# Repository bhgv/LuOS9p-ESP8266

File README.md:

luOS9p
------

It is an OS for ESP8266 IoT microcontrollers based on Lua-RTOS-ESP8266. But it was significally checked, changed and expanded.

https://youtu.be/ojTmyH3cTSQ

[schemaic+pcb](pcb/eagle) (Eagle CAD)

Features
========
* Lua 5.3.4,
* Multithreading using Free-RTOS,
* UART (ttl rs232, com port),
* I2C,
* SPI,
* 16 PWMs (hardware),
* 16 PIOs,
* 5 ADC (3 up to 3v + 1 up to 1v + 1 used internally),
* 1 DAC (up to 3v),
* OLED screen,
* Keyboard with 8 buttons (cursor + 3 special + 1 external),
* GUI (menu based. using OLED and keyboard),
* Shell by remote (rs232) terminal,
* internal Editor of files (remote terminal),
* big set of easy to use shell commands (filesystem, ports, devices, network, server, other)
* net Ap and Sta modes,
* one command WiFi Sta search,
* PID regulator module,

* Webserver (with compressing):
  1. static HTML,
  1. CGI,
  1. WebSock (up to 5 connections),
  1. direct access to devices/ports using WebSock,

* 9p2000/Styx (Plan9/Inferno os) distributed network virtual file system + server:
  1. list of devices (ex: `ls /n/dev`),
  1. list of device's functions (ex: `cat /n/dev/pwm`),
  1. call a device's function (ex: `echo ch_val -i 5 -n 0.4 > /n/dev/pwm`),
  1. read the result of the function's call (ex: `<> /n/dev/pwm {echo ch_val -i 5 >[1=0]; read}`),
  1. read a file/folder list from the fisical filesystem of the device (ex: `ls /n/fs/html/js`),
  1. read/write/create files on the device's fisical filesystem (ex: `cat /n/fs/html/js/common.js` or `echo a Text > /n/fs/afile.txt`),
  1. create new folders on the device's fisical filesystem (ex: `mkdir /n/fs/new_folder`),
  1. remove files or folders from the fisical device's filesystem (ex: `rm /n/fs/html/a_file_or_folder`),
  1. RPC channel (synthetic file `/rpc`). it allows to send Lua chunk to the device, run it there and return the result. (ex: `<> /n/rpc {echo 'pwm[5] = 0.2; return "adc_1=", adc[1];' >[1=0]; read}`),
  1. user's CGI-like synthetic files. (ex: on the remote device: `styx.addfile("a_file", function(a) return a + 8; end);`, from the inferno-shell: `<> /n/a_file {echo -n 10.9 >[1=0]; read}`).

* PC-Studio for easyer upload/download/edit files into/from/on the luOS9p embedded filesystem. also PC-Studio contains remote terminal for luOS9p and other features (in the future). It is written on the Lua and may be edited/expanded easily. It also contains a plugin system for extensions, but it isn't activated for now.

How to build
============
```
./bld.sh    # build
./flash.sh  # flash
```

How to build PC-Studio
======================
```
cd pc-studio
./bld.sh
```

How to run PC-Studio
====================
```
cd pc-studio/bld
./prg
```

How to run Styx server
======================
In the device's console or from the lua script:
```
thread.start( styx.loop )
```
Or just select `Styx server` on the device's gui if you are using LuOS9p-PCB (or other with ported GUI driver)

In the inferno shell/script/limbo etc:
```
mount -A tcp!<IP address of your device>!6701 /n
```
Now your IoT device's styx virtual fs is mounted to `/n` folder, including branches for drivers `/dev` and for access to the fisical filesystem of the your IoT device `/fs`. Use it as a regular filesystem.

A special board for the luOS9p
==============================
For this OS was designed a [special PCB](pcb/eagle/) that included all the necessary hardware/drivers and supports all the features of the OS.

But the OS may be used with the most esp8266-based boards (maybe with changes in the drivers part of the OS according to the target hardware)

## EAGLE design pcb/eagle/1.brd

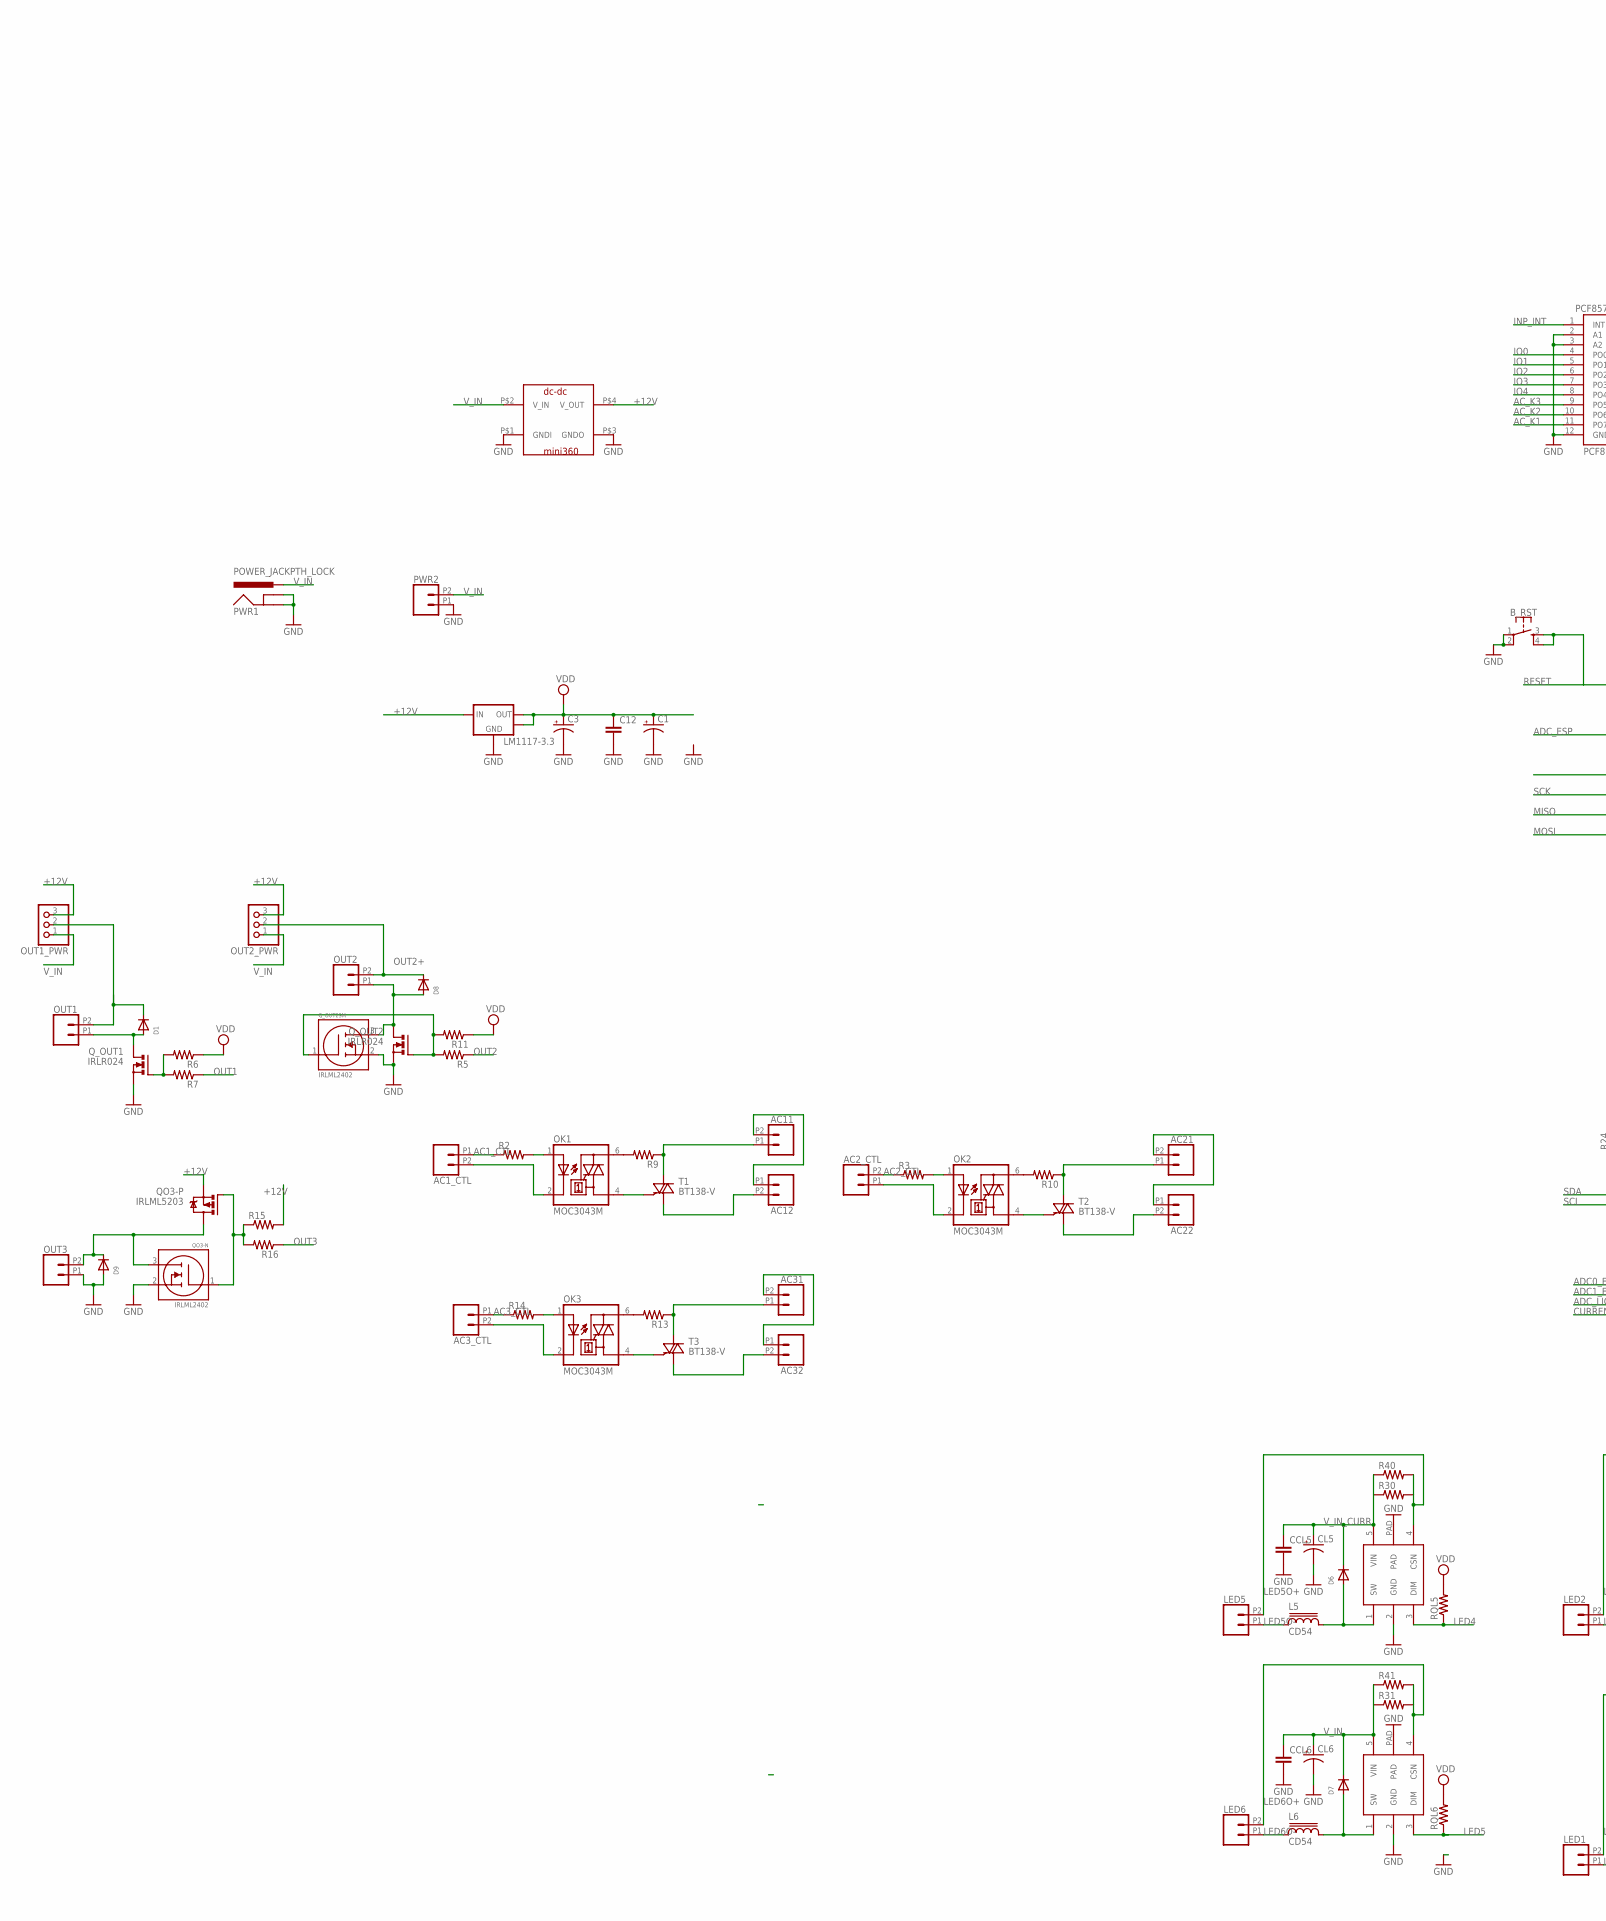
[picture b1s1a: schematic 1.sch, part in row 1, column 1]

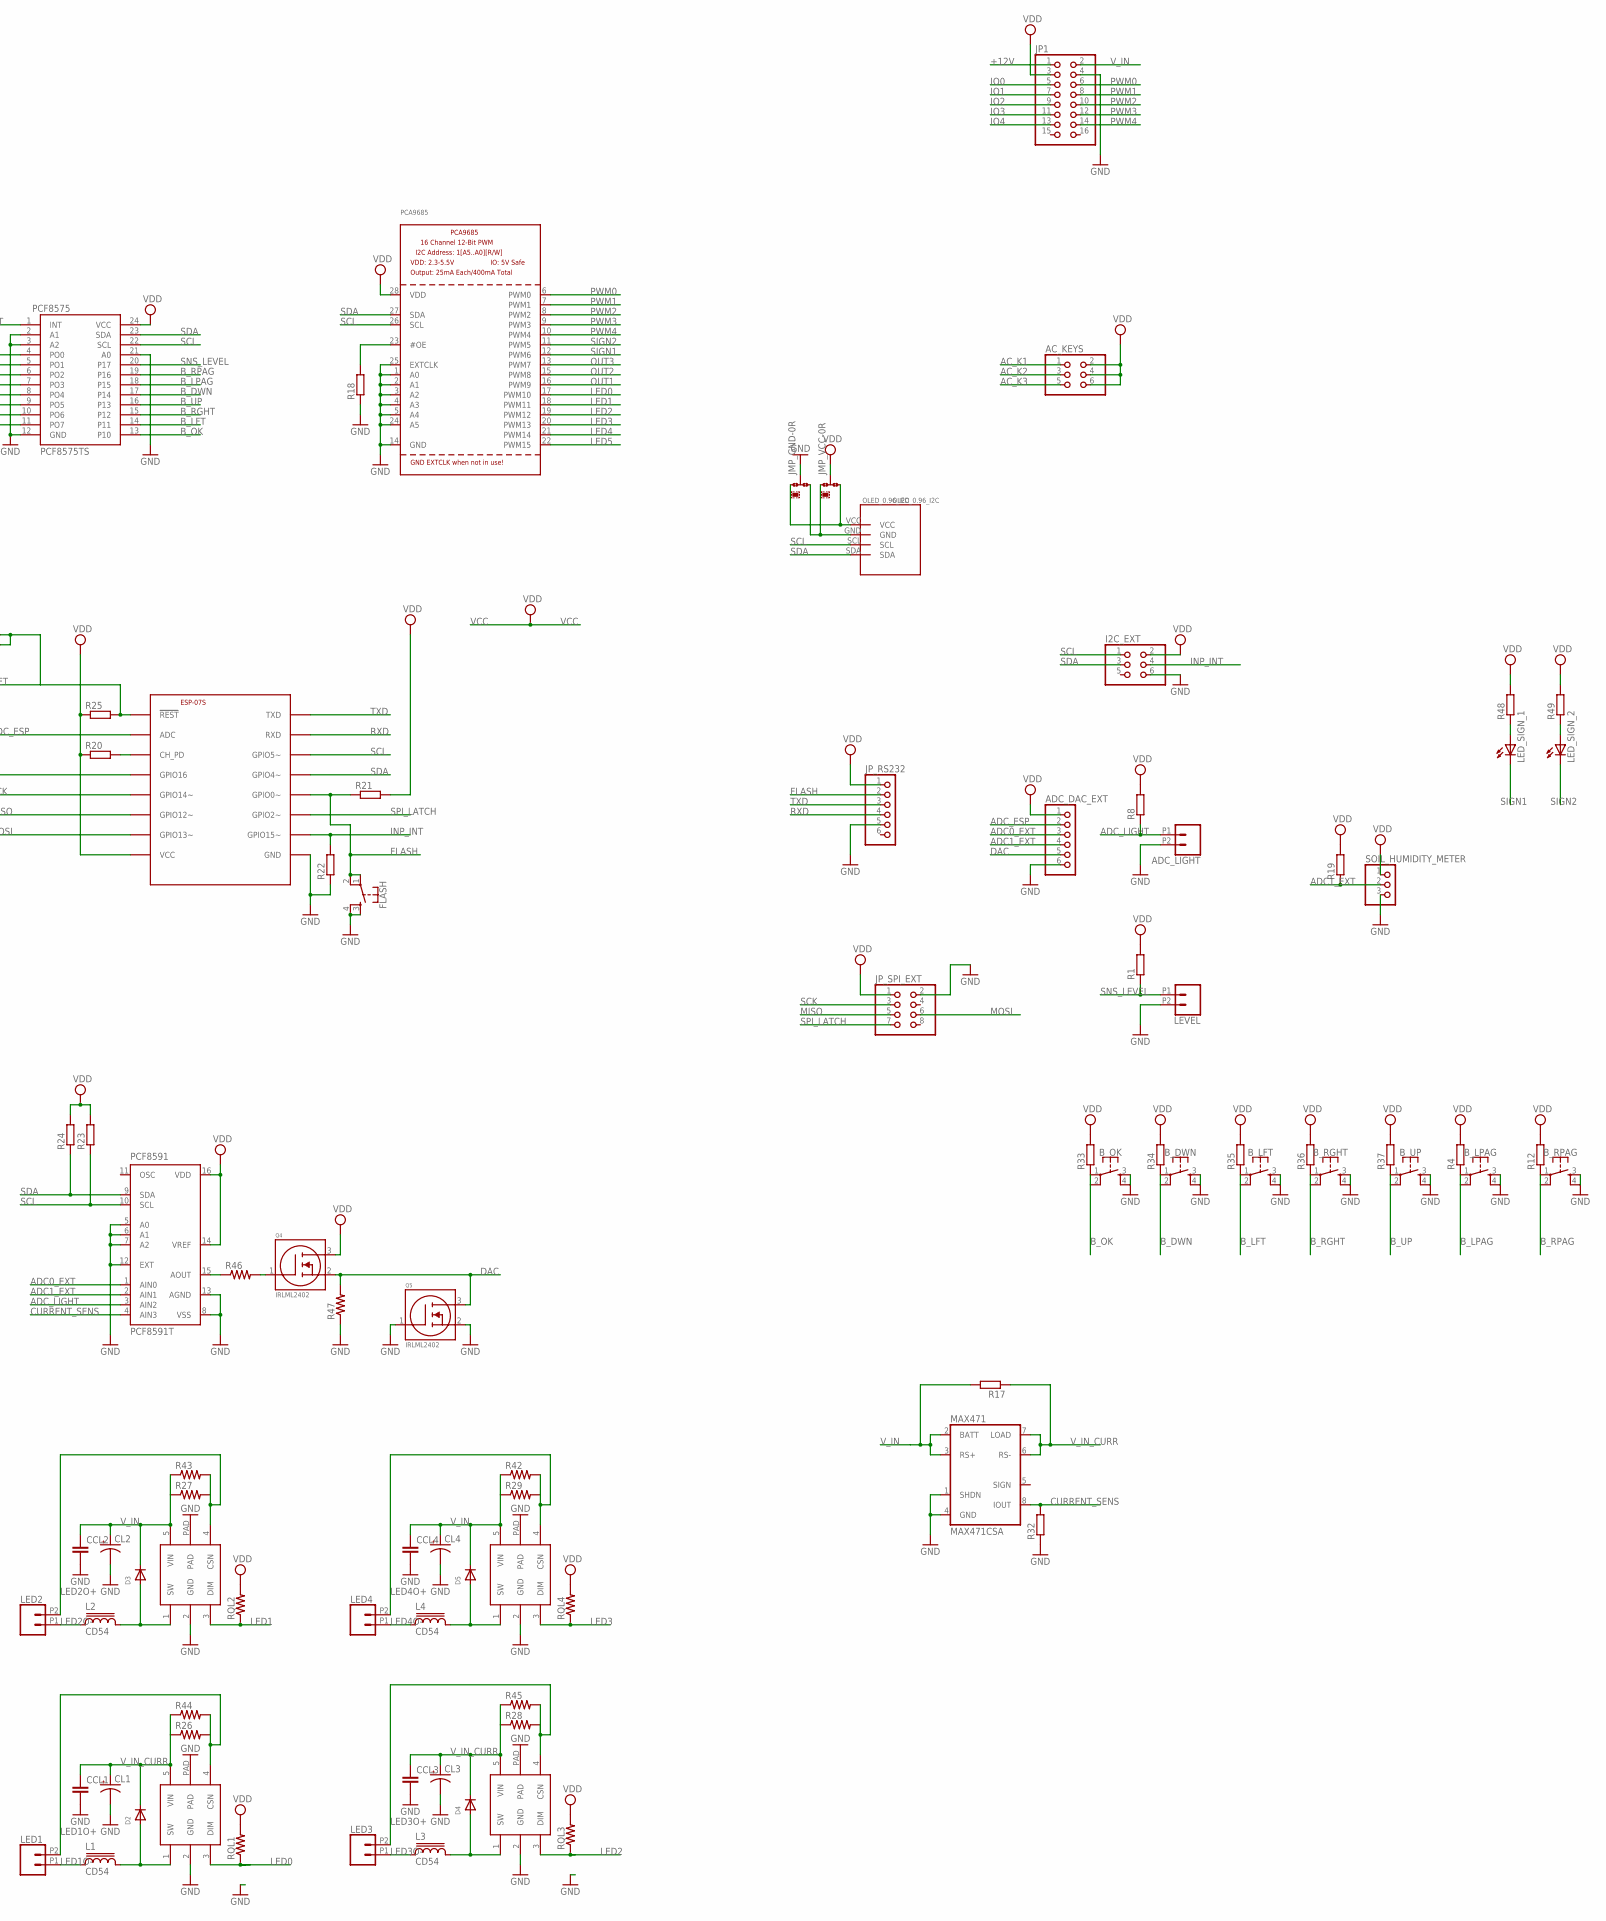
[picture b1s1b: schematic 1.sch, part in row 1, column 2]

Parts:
AC1_CTL, AC2_CTL, AC3_CTL, AC11, AC12, AC21, AC22, AC31, AC32: CONN_022.54MM_SCREWTERM; 1X02_2.54_SCREWTERM
AC_KEYS: PINHD-2X3; 2X03
ADC_DAC_EXT: PINHD-1X6; 1X06
ADC_LIGHT: CONN_022.54MM_SCREWTERM; 1X02_2.54_SCREWTERM
B_DWN: MOMENTARY-SWITCH-SPST-2-SMD-5.2MM; TACTILE_SWITCH_SMD_5.2MM
B_LFT: MOMENTARY-SWITCH-SPST-2-SMD-5.2MM; TACTILE_SWITCH_SMD_5.2MM
B_LPAG: MOMENTARY-SWITCH-SPST-2-SMD-5.2MM; TACTILE_SWITCH_SMD_5.2MM
B_OK: MOMENTARY-SWITCH-SPST-2-SMD-5.2MM; TACTILE_SWITCH_SMD_5.2MM
B_RGHT: MOMENTARY-SWITCH-SPST-2-SMD-5.2MM; TACTILE_SWITCH_SMD_5.2MM
B_RPAG: MOMENTARY-SWITCH-SPST-2-SMD-5.2MM; TACTILE_SWITCH_SMD_5.2MM
B_RST: MOMENTARY-SWITCH-SPST-2-SMD-5.2MM; TACTILE_SWITCH_SMD_5.2MM
B_UP: MOMENTARY-SWITCH-SPST-2-SMD-5.2MM; TACTILE_SWITCH_SMD_5.2MM
C1, C3: CPOL-US153CLV-0505; 153CLV-0505
C12: C-EUC0805; C0805
CCL1, CCL2, CCL3, CCL4, CCL5, CCL6: C-EUC0805K; C0805K
CL1, CL2, CL3, CL4, CL5, CL6: CPOL-US153CLV-0605; 153CLV-0605
D1, D2, D3, D4, D5, D6, D7, D8, D9: DIODESMA; SMADIODE
ESP-07S: ESP8266-08; ESP-08
FLASH: MOMENTARY-SWITCH-SPST-2-SMD-5.2MM; TACTILE_SWITCH_SMD_5.2MM
I2C_EXT: PINHD-2X3; 2X03
JMP_GND: 0R-JUMPA; A0R-JMP
JMP_VCC: 0R-JUMPA; A0R-JMP
JP1: PINHD-2X8; 2X08
JP_RS232: PINHD-1X6; 1X06
JP_SPI_EXT: PINHD-2X4; 2X04
L1, L2, L3, L4, L5, L6: CD54
LED1, LED2, LED3, LED4, LED5, LED6: CONN_022.54MM_SCREWTERM; 1X02_2.54_SCREWTERM
LED_SIGN_1, LED_SIGN_2: LEDCHIP-LED0805; CHIP-LED0805
LEVEL: CONN_022.54MM_SCREWTERM; 1X02_2.54_SCREWTERM
LM1117-3.3: LM1117-3.3; SOT223
MAX471: MAX471CSA; SO08
OK1, OK2, OK3: MOC3043M; DIL06
OLED_0.96_I2C: OLED_0.96_I2C
OUT1, OUT2, OUT3: CONN_022.54MM_SCREWTERM; 1X02_2.54_SCREWTERM
OUT1_PWR, OUT2_PWR: PINHD-1X3; 1X03
PCA9685: PCA9685; TSSOP28
PCF8575: PCF8575TS; SSOP24
PCF8591: PCF8591T; SO16W
PWR1: POWER_JACKPTH_LOCK; POWER_JACK_PTH_LOCK
PWR2: CONN_022.54MM_SCREWTERM; 1X02_2.54_SCREWTERM
Q4, Q5: IRLML2402; SOT23
QO3-N: IRLML2402; SOT23
QO3-P: IRLML5203; MICRO3
Q_OUT1, Q_OUT2: IRLR024; D-PAK_TO252AA
Q_OUT2SM: IRLML2402; SOT23
R1, R4, R8, R12, R17, R18, R19, R20, R21, R22, R23, R24, R25, R32, R33, R34, R35, R36, R37, R48, R49: R-EU_M0805; M0805
R2, R3, R5, R6, R7, R9, R10, R11, R13, R14, R15, R16: RESISTOR0805-RES; 0805
R26, R27, R28, R29, R30, R31, R40, R41, R42, R43, R44, R45, R46, R47: RESISTOR; 0805
RQL1, RQL2, RQL3, RQL4, RQL5, RQL6: RESISTOR; 0805
SOIL_HUMIDITY_METER: PINHD-1X3; 1X03
T1, T2, T3: BT138-V; TO220BV
U$6, U$7, U$8, U$9, U$10, U$13: PT4115; SOT89-5
U$12: MINI360

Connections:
+12V: JP1.1, LM1117-3.3.3 (IN), OUT1_PWR.3, OUT2_PWR.3, QO3-P.2 (S), R15.2, U$12.P$4 (V_OUT)
AC1_CTL: AC1_CTL.P1 (1), R2.1
AC2_CTL: AC2_CTL.P2 (2), R3.1
AC3_CTL: AC3_CTL.P1 (1), R14.1
AC11: AC11.P1 (1), R9.1, T1.T2 (A2)
AC12: AC12.P2 (2), T1.T1 (A1)
AC13: AC11.P2 (2), AC12.P1 (1)
AC21: AC21.P1 (1), R10.1, T2.T2 (A2)
AC22: AC22.P2 (2), T2.T1 (A1)
AC23: AC21.P2 (2), AC22.P1 (1)
AC31: AC31.P1 (1), R13.1, T3.T2 (A2)
AC32: AC32.P2 (2), T3.T1 (A1)
AC33: AC31.P2 (2), AC32.P1 (1)
AC_K1: AC_KEYS.1, PCF8575.11 (PO7)
AC_K2: AC_KEYS.3, PCF8575.10 (PO6)
AC_K3: AC_KEYS.5, PCF8575.9 (PO5)
ADC0_EXT: ADC_DAC_EXT.3, PCF8591.1 (AIN0)
ADC1_EXT: ADC_DAC_EXT.4, PCF8591.2 (AIN1), R19.1, SOIL_HUMIDITY_METER.2
ADC_ESP: ADC_DAC_EXT.2, ESP-07S.ADC
ADC_LIGHT: ADC_LIGHT.P1 (1), PCF8591.3 (AIN2), R8.1
B_DWN: B_DWN.1, B_DWN.2, PCF8575.17 (P14), R34.1
B_LFT: B_LFT.1, B_LFT.2, PCF8575.14 (P11), R35.1
B_LPAG: B_LPAG.1, B_LPAG.2, PCF8575.18 (P15), R4.1
B_OK: B_OK.1, B_OK.2, PCF8575.13 (P10), R33.1
B_RGHT: B_RGHT.1, B_RGHT.2, PCF8575.15 (P12), R36.1
B_RPAG: B_RPAG.1, B_RPAG.2, PCF8575.19 (P16), R12.1
B_UP: B_UP.1, B_UP.2, PCF8575.16 (P13), R37.1
CURRENT_SENS: MAX471.8 (IOUT), PCF8591.4 (AIN3), R32.2
DAC: ADC_DAC_EXT.5, Q4.2 (SOURCE), Q5.3 (DRAIN), R47.2
FLASH: ESP-07S.GPIO0 (GPIO0~), FLASH.1, FLASH.2, JP_RS232.2, R21.1
GND: ADC_DAC_EXT.6, ADC_LIGHT.P2 (2), B_DWN.3, B_DWN.4, B_LFT.3, B_LFT.4, B_LPAG.3, B_LPAG.4, B_OK.3, B_OK.4, B_RGHT.3, B_RGHT.4, B_RPAG.3, B_RPAG.4, B_RST.1, B_RST.2, B_UP.3, B_UP.4, C1.-, C3.-, C12.2, CCL1.2, CCL2.2, CCL3.2, CCL4.2, CCL5.2, CCL6.2, CL1.-, CL2.-, CL3.-, CL4.-, CL5.-, CL6.-, D9.A, ESP-07S.GND, FLASH.3, FLASH.4, I2C_EXT.6, JMP_GND.2, JP1.4, JP_RS232.5, JP_SPI_EXT.2, LEVEL.P2 (2), LM1117-3.3.1 (GND), MAX471.1 (SHDN), MAX471.4 (GND), OUT3.P1 (1), PCA9685.1 (A0), PCA9685.2 (A1), PCA9685.3 (A2), PCA9685.4 (A3), PCA9685.5 (A4), PCA9685.14 (GND), PCA9685.24 (A5), PCA9685.25 (EXTCLK), PCF8575.2 (A1), PCF8575.3 (A2), PCF8575.12 (GND), PCF8575.21 (A0), PCF8591.5 (A0), PCF8591.6 (A1), PCF8591.7 (A2), PCF8591.8 (VSS), PCF8591.12 (EXT), PCF8591.13 (AGND), PWR1.GND, PWR1.GNDBREAK, PWR2.P1 (1), Q5.1 (GATE), Q5.2 (SOURCE), QO3-N.2 (SOURCE), Q_OUT1.3 (SOURCE), Q_OUT2.3 (SOURCE), Q_OUT2SM.2 (SOURCE), R18.1, R22.1, R32.1, R47.1, SOIL_HUMIDITY_METER.3, U$6.2 (GND), U$6.PAD, U$7.2 (GND), U$7.PAD, U$8.2 (GND), U$8.PAD, U$9.2 (GND), U$9.PAD, U$10.2 (GND), U$10.PAD, U$12.P$1 (GNDI), U$12.P$3 (GNDO), U$13.2 (GND), U$13.PAD
INP_INT: ESP-07S.GPIO15 (GPIO15~), I2C_EXT.4, PCF8575.1 (INT), R22.2
IO0: JP1.5, PCF8575.4 (PO0)
IO1: JP1.7, PCF8575.5 (PO1)
IO2: JP1.9, PCF8575.6 (PO2)
IO3: JP1.11, PCF8575.7 (PO3)
IO4: JP1.13, PCF8575.8 (PO4)
LED0: PCA9685.17 (PWM10), RQL1.1, U$13.3 (DIM)
LED1: PCA9685.18 (PWM11), RQL2.1, U$6.3 (DIM)
LED1O+: LED1.P2 (2), R26.2, R44.2, U$13.4 (CSN)
LED1O-: L1.1, LED1.P1 (1)
LED1_SW: D2.A, L1.2, U$13.1 (SW)
LED2: PCA9685.19 (PWM12), RQL3.1, U$7.3 (DIM)
LED2O+: LED2.P2 (2), R27.2, R43.2, U$6.4 (CSN)
LED2O-: L2.1, LED2.P1 (1)
LED2_SW: D3.A, L2.2, U$6.1 (SW)
LED3: PCA9685.20 (PWM13), RQL4.1, U$8.3 (DIM)
LED3O+: LED3.P2 (2), R28.2, R45.2, U$7.4 (CSN)
LED3O-: L3.1, LED3.P1 (1)
LED3_SW: D4.A, L3.2, U$7.1 (SW)
LED4: PCA9685.21 (PWM14), RQL5.1, U$9.3 (DIM)
LED4O+: LED4.P2 (2), R29.2, R42.2, U$8.4 (CSN)
LED4O-: L4.1, LED4.P1 (1)
LED4_SW: D5.A, L4.2, U$8.1 (SW)
LED5: PCA9685.22 (PWM15), RQL6.1, U$10.3 (DIM)
LED5O+: LED5.P2 (2), R30.2, R40.2, U$9.4 (CSN)
LED5O-: L5.1, LED5.P1 (1)
LED5_SW: D6.A, L5.2, U$9.1 (SW)
LED6O+: LED6.P2 (2), R31.2, R41.2, U$10.4 (CSN)
LED6O-: L6.1, LED6.P1 (1)
LED6_SW: D7.A, L6.2, U$10.1 (SW)
MISO: ESP-07S.GPIO12 (GPIO12~), JP_SPI_EXT.5
MOSI: ESP-07S.GPIO13 (GPIO13~), JP_SPI_EXT.6
unnamed: JMP_GND.1, JMP_VCC.3, OLED_0.96_I2C.VCC
unnamed: JMP_GND.3, JMP_VCC.1, OLED_0.96_I2C.GND
unnamed: LED_SIGN_1.A, R48.1
unnamed: LED_SIGN_2.A, R49.1
unnamed: AC1_CTL.P2 (2), OK1.2 (C)
unnamed: PCA9685.23 (#OE), R18.2
unnamed: Q_OUT2.1 (GATE), Q_OUT2SM.1 (GATE), R5.2, R11.2
unnamed: Q_OUT1.1 (GATE), R6.2, R7.2
unnamed: QO3-N.1 (GATE), QO3-P.1 (G), R15.1, R16.2
unnamed: AC3_CTL.P2 (2), OK3.2 (C)
unnamed: OK1.1 (A), R2.2
unnamed: OK1.4 (A1), T1.G
unnamed: ESP-07S.CH_PD, R20.2
unnamed: OK1.6 (A2), R9.2
unnamed: OK2.4 (A1), T2.G
unnamed: OK2.6 (A2), R10.2
unnamed: OK2.1 (A), R3.2
unnamed: OK3.4 (A1), T3.G
unnamed: OK3.6 (A2), R13.2
unnamed: PCF8591.15 (AOUT), R46.1
unnamed: Q4.1 (GATE), R46.2
unnamed: AC2_CTL.P1 (1), OK2.2 (C)
unnamed: OK3.1 (A), R14.2
OUT1: PCA9685.16 (PWM9), R7.1
OUT1+: D1.C, OUT1.P2 (2), OUT1_PWR.2
OUT1-: D1.A, OUT1.P1 (1), Q_OUT1.2 (DRAIN)
OUT2: PCA9685.15 (PWM8), R5.1
OUT2+: D8.C, OUT2.P2 (2), OUT2_PWR.2
OUT2-: D8.A, OUT2.P1 (1), Q_OUT2.2 (DRAIN), Q_OUT2SM.3 (DRAIN)
OUT3: PCA9685.13 (PWM7), R16.1
OUT3+: D9.C, OUT3.P2 (2), QO3-N.3 (DRAIN), QO3-P.3 (D)
PWM0: JP1.6, PCA9685.6 (PWM0)
PWM1: JP1.8, PCA9685.7 (PWM1)
PWM2: JP1.10, PCA9685.8 (PWM2)
PWM3: JP1.12, PCA9685.9 (PWM3)
PWM4: JP1.14, PCA9685.10 (PWM4)
RESET: B_RST.3, B_RST.4, ESP-07S.REST (!REST), R25.2
RXD: ESP-07S.RXD, JP_RS232.4
SCK: ESP-07S.GPIO14 (GPIO14~), JP_SPI_EXT.3
SCL: ESP-07S.GPIO4 (GPIO5~), I2C_EXT.1, OLED_0.96_I2C.SCL, PCA9685.26 (SCL), PCF8575.22 (SCL), PCF8591.10 (SCL), R23.1
SDA: ESP-07S.GPIO5 (GPIO4~), I2C_EXT.3, OLED_0.96_I2C.SDA, PCA9685.27 (SDA), PCF8575.23 (SDA), PCF8591.9 (SDA), R24.1
SIGN1: LED_SIGN_1.C, PCA9685.12 (PWM6)
SIGN2: LED_SIGN_2.C, PCA9685.11 (PWM5)
SNS_LEVEL: LEVEL.P1 (1), PCF8575.20 (P17), R1.1
SPI_LATCH: ESP-07S.GPIO2 (GPIO2~), JP_SPI_EXT.7
TXD: ESP-07S.TXD, JP_RS232.3
VDD: AC_KEYS.2, AC_KEYS.4, AC_KEYS.6, ADC_DAC_EXT.1, C1.+, C3.+, C12.1, ESP-07S.VCC, I2C_EXT.2, JMP_VCC.2, JP1.3, JP_RS232.1, JP_SPI_EXT.1, LM1117-3.3.2 (OUT), LM1117-3.3.4 (MASS), PCA9685.28 (VDD), PCF8575.24 (VCC), PCF8591.14 (VREF), PCF8591.16 (VDD), Q4.3 (DRAIN), R1.2, R4.2, R6.1, R8.2, R11.1, R12.2, R19.2, R20.1, R21.2, R23.2, R24.2, R25.1, R33.2, R34.2, R35.2, R36.2, R37.2, R48.2, R49.2, RQL1.2, RQL2.2, RQL3.2, RQL4.2, RQL5.2, RQL6.2, SOIL_HUMIDITY_METER.1
V_IN: CCL2.1, CCL4.1, CCL6.1, CL2.+, CL4.+, CL6.+, D3.C, D5.C, D7.C, JP1.2, MAX471.2 (BATT), MAX471.3 (RS+), OUT1_PWR.1, OUT2_PWR.1, PWR1.PWR, PWR2.P2 (2), R17.2, R27.1, R29.1, R31.1, R41.1, R42.1, R43.1, U$6.5 (VIN), U$8.5 (VIN), U$10.5 (VIN), U$12.P$2 (V_IN)
V_IN_CURR: CCL1.1, CCL3.1, CCL5.1, CL1.+, CL3.+, CL5.+, D2.C, D4.C, D6.C, MAX471.6 (RS-), MAX471.7 (LOAD), R17.1, R26.1, R28.1, R30.1, R40.1, R44.1, R45.1, U$7.5 (VIN), U$9.5 (VIN), U$13.5 (VIN)

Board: 2 copper layers, 154 parts (70 on the bottom side), 112 nets, no tracks yet.

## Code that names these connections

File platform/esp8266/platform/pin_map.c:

#include "pin_map.h"
#include "eagle_soc.h"
#include "mem.h"
#include "etstimer.h"
#include "osapi.h"

uint32_t pin_mux[GPIO_PIN_NUM];
uint8_t  pin_num[GPIO_PIN_NUM];
uint8_t  pin_func[GPIO_PIN_NUM];
#ifdef GPIO_INTERRUPT_ENABLE
uint8_t  pin_num_inv[GPIO_PIN_NUM_INV];
uint8_t  pin_int_type[GPIO_PIN_NUM];
#endif

typedef struct {
  int8  mux;
  uint8 num;
  uint8 func;
  uint8 intr_type;
} pin_rec;
#define DECLARE_PIN(n,p) { (PERIPHS_IO_MUX_##p##_U - PERIPHS_IO_MUX), n, FUNC_GPIO##n, GPIO_PIN_INTR_DISABLE}
static const pin_rec pin_map[] = {
   {PAD_XPD_DCDC_CONF  - PERIPHS_IO_MUX, 16, 0, GPIO_PIN_INTR_DISABLE},
    DECLARE_PIN( 5, GPIO5),
    DECLARE_PIN( 4, GPIO4),
    DECLARE_PIN( 0, GPIO0),
    DECLARE_PIN( 2, GPIO2),
    DECLARE_PIN(14, MTMS),
    DECLARE_PIN(12, MTDI),
    DECLARE_PIN(13, MTCK),
    DECLARE_PIN(15, MTDO),
    DECLARE_PIN( 3, U0RXD),
    DECLARE_PIN( 1, U0TXD),
    DECLARE_PIN( 9, SD_DATA2),
    DECLARE_PIN(10, SD_DATA3)
};
void get_pin_map(void) {
  /*
   * Flash copy of the pin map.  This has to be copied to RAM to be accessible from the ISR.
   * Note that the mux field is a signed offset from PERIPHS_IO_MUX to allow the whole struct
   * to be stored in a single 32-bit record.
   */
  int i;
  /* Take temporary stack copy to avoid unaligned exceptions on Flash version */
  pin_rec pin[GPIO_PIN_NUM];
  memcpy(pin, pin_map, sizeof(pin_map) );

  for (i=0; i<GPIO_PIN_NUM; i++) {
    pin_mux[i]  = pin[i].mux + PERIPHS_IO_MUX;
    pin_func[i] = pin[i].func;
    pin_num[i]  = pin[i].num;
#ifdef GPIO_INTERRUPT_ENABLE
    pin_num_inv[pin_num[i]] = i;
    pin_int_type[i]         = pin[i].intr_type;
#endif
  }
}

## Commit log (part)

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2016-09-20 Removed some compilation warnings
2016-09-20 Removed unused files
2016-09-21 Added math, os, and tmr Lua modules
2016-09-21 Add .gitignore file
2016-09-21 Removed .DS_Store files
2016-09-21 UART driver, removed built-in debug functions, added syslogmessages. Added pin definitions in cpu driver.
2016-09-22 Added Lua pio module. Resolved some general bugs.
2016-09-22 Added Lua thread module
2016-09-22 Added os.sleep function to Lua os module
2016-09-23 Implementation of cpu_reset for ESP8266
2016-09-23 Add mkspiffs util for make an spiffs image and add to the firmware's image
2016-09-23 Add spiffs_image directory
2016-09-23 Removed mkspiffs subproject
2016-09-23 Add mkspiffs sources
2016-09-23 Make spiffs image and flash to ESP8266 with firmware
2016-09-27 Added open, read, write syscalls ... Resolved some bugs
2016-09-27 Removed compilation warnings
2016-09-27 lbaselib now uses rotables
2016-09-27 Add some memory optimizations in thread library
2016-09-27 Added editor sources (not working)
2016-09-27 Bug resolved on luaos_pushline (free on read only memory)
2016-09-28 Resolved some rotable bugs. Add io library.
2016-09-28 Add string library
2016-09-28 Added coroutine library
2016-09-28 Add vApplicationStackOverflowHook and vAssertCalled hooks
2016-09-29 More elegant way for launch garbage collector when heap alloc functions fails
2016-09-30 Ported LuaOS thread safe signal management
2016-09-30 Show error on Lua thread fail
2016-09-30 Memory optimizations
2016-10-02 Signal management simplification, more available RAM
2016-10-03 Some optimizations
2016-10-03 Bug resolved in gpio_pin_pullup/pulldwn,nopull gpio driver
2016-10-05 Some memory optimizations
2016-10-05 uart driver, uart0 and uart2 don't share rx queue now
2016-10-05 When run a script don't exec dofile intro a thread
2016-10-05 Memory optimizations in Lora driver
2016-10-06 In try function when error is catched throw an error if catched function fails
2016-10-06 Add os.luarunning Lua function, with this function a script can know if it's executed from autorun.lua (if false) or from Lua main thread (if true).
2016-10-06 lua_running is set after bootscripts are executed
2016-10-06 Added luainterpreter function to OS lib
2016-10-07 uxSetLuaState is called in pthread functions when tread is created, not in lua thread module, this assigns the correct Lua state in the TCB.
2016-10-07 Add resetreason in OS Module (not working)
2016-10-07 Add LuaOS state management function for save RAM
2016-10-07 Added LuaOS status management for save RAM. Improved detection of don't run boot scripts when booting
2016-10-07 status variabl _syscalls_inited moved to LuaOS status management
2016-10-07 Comment unused resource management areas
2016-10-08 New folder structure for multiplatform compile
2016-10-10 Add newlib sources
2016-10-10 Removed newlib
2016-10-10 Removed copy files from build in newlib build script
2017-07-02 now it runs on esp8266. a few errors were checked.
2017-07-03 continue working on runability. net, spiffs now work
2017-10-06 i2c oled ssd1306 supported using u8g library (u8g lua object). i2c lua module & i2c support. new easier system to register a C module. new spiffs lib from esp32 branch. in many parts code was synchro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
2017-10-13 changes in the structure of sources
2017-10-14 added driver and lua module for pca9685 pwm chip. pwm module from lua
2017-10-15 pcf8591 adc-dac driver and lua module ad was added
2017-10-15 adc & pwm modules lua interfaces and internal structure were a little changed to more convenient (as reading/writing module fields). data is float in percent - 0.0-100.0
2017-10-17 added support of pcf8575 gpio chip. lua module - 'gpio'
2017-10-20 tloop lua module was added to organise main GUI loop, disp lua module was added instead u8g as it simpler and consumes lower memory, lua thread max stacks become bigger, luos9 GUI first steps (folder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
2017-10-20 gui works. made DAC val readable. checkssome errors
2017-10-21 cont working on gui and adc
2017-10-21 big work on pcf8591 driver. now it seems as workable. i2c internal delays now are changeable and speed of all i2c drivers/modules now much increased
2017-10-22 last commit before the implementing of gui module in C
2017-10-22 'gui' lua C-module now ready to use. interface become faster, memory consumption become lower
2017-10-24 workable 'net' lua module + example of use in the autorun.lua
2017-10-24 added fonts support for 'oled' and 'gui' classes
2017-10-28 a try to add simple web/ws server. also from lua can get internal ADC 'adc.Int', lua 'net' obj was broken to 'sock' and 'net' objs
2017-10-28 check the suffix of uri file and use different responce headers. (web/ws server)
2017-11-01 +- reenterable and workable web/ws server with significally lower by lwip-tcp memory consumption. were changed some lwip tcp related parameters. lua 'net' package now broken into 'net', 'sock', 'http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
2017-11-02 html/ws server optimisations. some changes in lwip config to lowering of max net connections to lower of used memory
2017-11-02 spiffs logic block now experimentally become 4096 instead of 8192 to lesser memory consumption
2017-11-03 lua CGI and GET parameters handling (first steps) were added
2017-11-05 support of lua-cgi for websocket conversation, liolib was a little changed to decrease memory consumption, mutex was added to spiffs_ops, name of os was chaged to 'luOS9'
2017-11-08 some works on stability and lower memory consumption. little other changes
2017-11-15 big work on httpd & whole system stability. added net/socket errors handler/executor, lowered memory consumption, gdb caller (gdb.sh), more convenient structure of progect and other good things
2017-11-17 httpd module was splitted to couple of sub-files by their function. checked some mistakes. added .html files to check pio/pwm/adc/dac/lua-cgi functionality. also they may be used to control different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
2017-11-18 from HTML example/control files were separated common CSS and JS parts, but server can upload only 2 included in a html files (1 css + 1 js or 2 css or 2 js) yet
2017-11-18 websock part of httpd supports up to 3 connections now
2017-11-18 file & lua-cgi executors were separated from httpd to different files and couple of functions
2017-11-21 httpd was re-made to support up to 3 independed html input connections and up to 3 independed (but only 1 ws to 1 ip) in/out websock connections simultaneously. big work on stability and removing mem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
2017-11-26 wifi AP ( net.ap('SSID', 'PASS') ) added experimentally. also added lpeg lua module
2017-11-30 more stable ap+server working. automatic start of AP after 20s of non-connected station
2017-12-03 ability to wifi nets search was added ( net.search() )
2017-12-10 + modules spi (spi devs), os.edit (to edit files), data & data_io (to manipulate of binary data), sjson, mqtt (sjson & mqtt are disabled by default because of large mem consumption). continue tuning 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
2017-12-10 forgot to add luadata & luadata_io modules. a few fixes
2017-12-18 added PID lua module, to Gui lua module added timer callback functionality for dinamic interfaces, added new demo lua script to use module as a Solder station (also for checking of the PID module). r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
2017-12-23 GUI redrawing scheme and callback timings were changed. calling scheme of PID's ticks was changed to increase stability (wdt rst). different changes & fixes in GUI, Tloop, PID modules and some lua gu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
2017-12-30 first steps of PC-Studio for exchange of files, editing, terminal, other. httpd now compresses pages (removes spaces, tabs and cr) before send them.
2018-01-02 Readme.md was added
2018-01-03 added Styx / 9p remote file protocol/server as experiment
2018-01-07 Styx now shows list of lua rotables as /dev 9p-filesystem. also it can show list of functions & constants of any rotable by reading its 9p-file. ex: cat /dev/pwm
2018-01-07 Stix now can call Dev functions writing messages and reading results of calls. Also Devs support different ops: 'list', 'call', 'res' etc
2018-01-09 Styx/9p: device's real file system: read/browse structure, read files
2018-01-09 Styx: styx now can delete remotelly files and folders on the device's fisical filesystem
2018-01-09 Styx: Write/Create capability for device's fisical filesystem files. basic but workable.
2018-01-10 Styx: lua module was broken to: devices, files, common and utils parts
2018-01-10 Styx: device's fisical filesistem (/fs): now it can read from file/folders, write to files, create file/folders, remove file/folders
2018-01-11 small updates, light checks & cosmetical changes
2018-01-11 README.md was updated. picture of LuOS9p-PCB was added
2018-01-13 Styx: RPC funtionality and virtual file for RPC was added to styx. root reading & small fixes in the styx
2018-01-14 Styx: checking in the Dev and RPC parts. Begin of works on synthetic styx files/folders like CGIs. different small checkings and changes
2018-01-14 Styx: user's CGI-like synthetic files as a way to RPC. they support parameters in the form matching to form of devices' functions calls. checking of RPC channel '/rpc', other small checkings
2018-01-19 a link to video-presentation was added
2018-01-19 PC-studio: logic of data receiving by UART was a little checked. light cleaning of oled lua modules. oled module's functions now return oled module itself for continuous calling like: oled.cls().prin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
2018-05-19 lua-callback for ext-key was added to gui module. it receives boolean parameter - state of the ext key
2018-05-23 added a possibility to load to external .PBM pictures from the flash-fs (). checked error an in the module. lowered memory consumption of the module.
2018-05-23 Revert "added a possibility to load to external .PBM pictures from the flash-fs (). checked error an in the module. lowered memory consumption of the module."
    This reverts commit dea77832d5ad7b5ebf77e52efd40f359f8370a2d.
2018-05-23 Revert "Revert "added a possibility to load to external .PBM pictures from the flash-fs (). checked error an in the module. lowered memory consumption of the module.""
    This reverts commit 4797db249d7ec9c37b5579da6e75b994bb1d89ed.
2018-07-21 schematic and pcb of the special board (Eagle CAD) were added
2018-09-11 checked a possible error with types and memory
2018-09-17 less of memory to gui. new example: greengarden light & water controller
2018-09-17 greengarden ctrlr scripts

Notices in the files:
parts and their libraries:
vreg-linear: 2009 Draw by Ivan A-R. License CC-BY-SA 3.0
SparkFun-Retired: Licensing: Creative Commons ShareAlike 4.0 International - https://creativecommons.org/licenses/by-sa/4.0
inductor-sumida: Copyright (C) 2008, Bob Starr
